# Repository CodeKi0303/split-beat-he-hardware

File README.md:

# Split-Beat HE · Hardware

codeki lab의 좌우 분리형 홀 이펙트 리듬게임 컨트롤러입니다. C86 4층 PCB는 좌우 각각 Hall 입력 7개와 기계식 입력·인코더를 지원합니다.

## 한 세트 주문

1. [PCB 제작 자료](manufacturing/pcb)의 Gerber/드릴 ZIP, BOM, CPL을 업로드합니다. 한 패널에 왼쪽과 오른쪽 각 1장이 들어 있습니다. 업체의 최소 수량과 실장 후 분리 옵션을 확인하세요.
2. 4층 1.6mm급, ENIG, 신호–GND–GND–신호 구성으로 견적을 받습니다. 제작 전 USB HS 차동 90Ω 목표와 공장 적층을 대조하고, **R609 한 자리만 미실장**과 하단 SWD 직각 헤더의 **긴 핀이 기판 안쪽**을 향하는지 확인합니다. KiCad 원본에 R609 패드가 남아 있습니다. CPL의 좌우 수직 노브 인코더와 SWD 헤더를 공장 DFM에서 확인하고, 수평 휠 TTC 엔코더는 별도로 구매해 직접 납땜합니다.
3. 알루미늄 5052 1.5mm [실제 조립 판](manufacturing/plates/as-built)을 상판 좌우·하판 좌우 각 1장 주문합니다. 상판은 은색 무광 아노다이징, 하판은 무처리로 제작했습니다. 상·하판 외곽을 맞춘 [수정 후보](manufacturing/plates/fit-candidate)는 실제 출력·조립 확인이 남아 있습니다.
4. [수평 휠 저장소](https://github.com/CodeKi0303/split-beat-he-wheel)에서 휠과 지지부, MR83ZZ 베어링, TTC Gold 엔코더 규격을 확인합니다. 수직 노브용 [베젤](manufacturing/knob-bezels), 스위치와 키캡, 나사·절연 와셔·스페이서도 준비합니다.

제작 묶음은 원본 업로드 자료의 공개용 복사본입니다. 공장 내부 CAM·견적·주문 화면과 계정 자료는 별도로 관리합니다. [PCB 제작 메모](manufacturing/pcb/README.md)에서 패널 분리와 실장 조건을 확인하세요.

## 조립과 사용

- [나사 체결 단면도](docs/fastener-assembly-sections.svg)의 A/B/C 위치를 기준으로 조립합니다. USB 개구부, 납땜 핀과 하판의 간격, 휠이 자유롭게 도는지 확인합니다.
- 새 보드는 [펌웨어의 SWD 초기 설치](https://github.com/CodeKi0303/split-beat-he-firmware/blob/main/C86-FIRST-FLASH.md)를 진행합니다.
- **PC → 왼쪽 PC용 USB-C**, **왼쪽 split 포트 → 오른쪽 split 포트** 순으로 연결합니다. 오른쪽 USB-C는 좌우 통신·전원용입니다. [Studio](https://studio.codekilab.com/)에서 캘리브레이션, 매핑, 작동점 및 Rapid Trigger를 설정합니다. [Studio 소스와 로컬 실행](https://github.com/CodeKi0303/split-beat-he-studio).

## 휠 가져오기

```sh
git clone --recurse-submodules https://github.com/CodeKi0303/split-beat-he-hardware.git
```

이미 내려받았다면 `git submodule update --init`으로 `modules/horizontal-wheel`을 받습니다. 서브모듈이 이 설계에 맞춰 검토한 휠 커밋을 고정합니다.

직접 만든 설계는 [CERN-OHL-P-2.0](LICENSE)입니다. `pcb/board/pcb-libs/`의 외부 풋프린트 고지는 해당 디렉터리에 보존합니다. 프로젝트 이력은 [codeki lab](https://codekilab.com/#keyboard-project)에서 볼 수 있습니다.

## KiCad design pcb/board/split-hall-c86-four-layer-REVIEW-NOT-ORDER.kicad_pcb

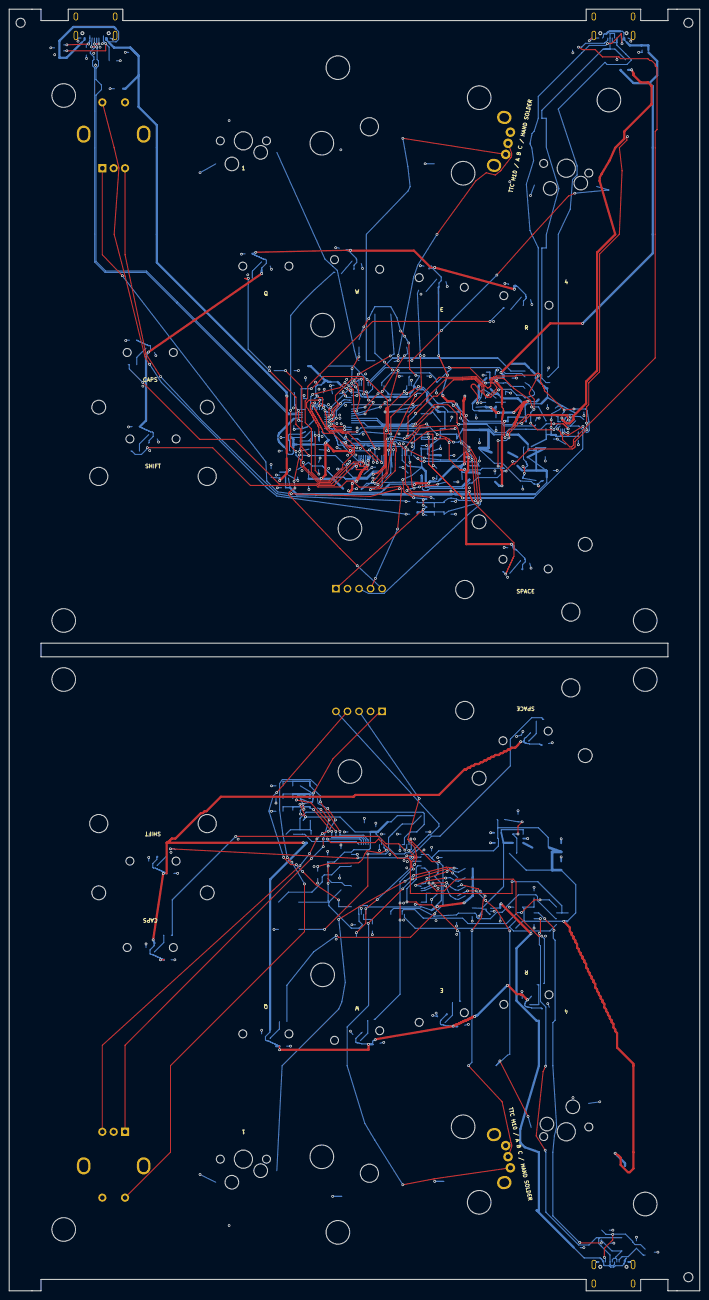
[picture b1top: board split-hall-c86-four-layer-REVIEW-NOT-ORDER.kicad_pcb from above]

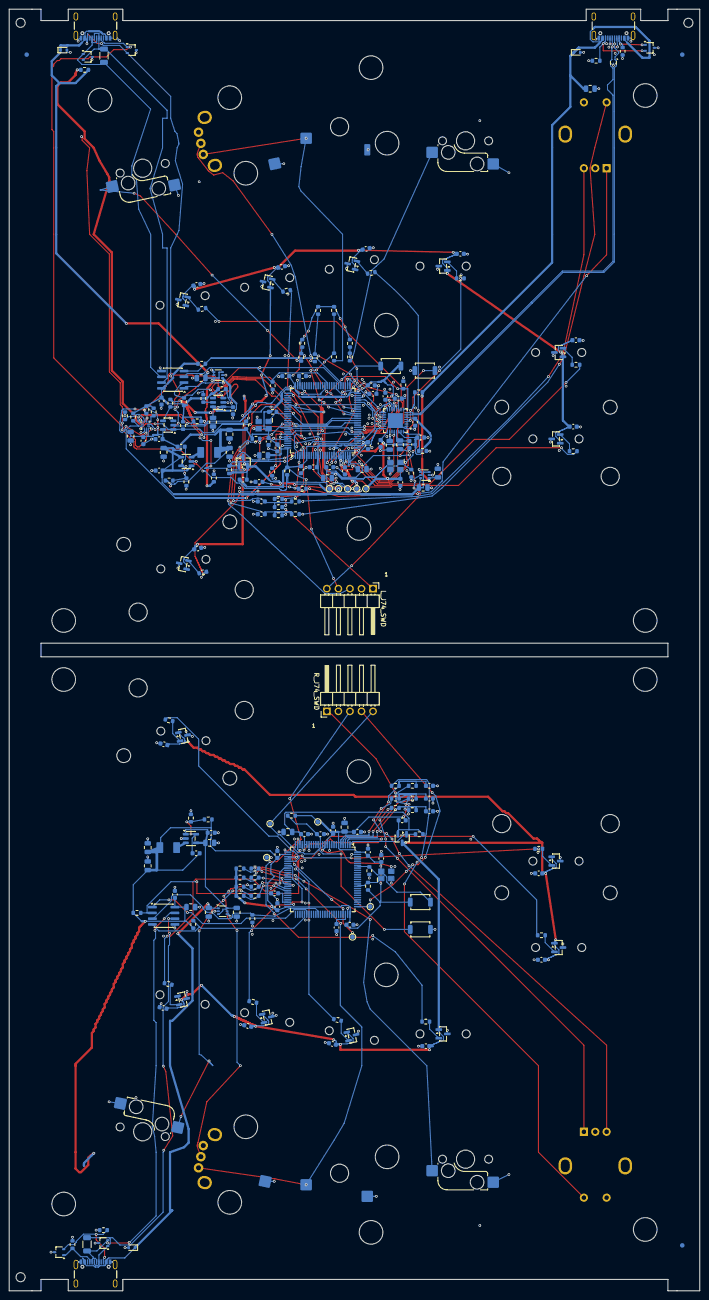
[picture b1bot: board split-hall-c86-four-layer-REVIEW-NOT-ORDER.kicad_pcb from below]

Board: 4 copper layers, 152.0 x 282.1 mm, 307 parts (236 on the bottom side), 143 nets.

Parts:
C211, C212, C221, C230, C231, C232, C233, C234, C236, C239, C311, C312, C321, C330, C331, C332, C333, C334, C336, C339, C410, C411, C412, C413, C414, C416, C418, C501, C551, C607, C608, C701, C1001, C1002, C1003, C1004, C1005, C1006, C1007, C1101, C1102, C1103, C1104, C1105, C1106, C1107: GRM188R72A104KA35D; C_0603_1608Metric
C220, C235, C320, C335, C415, C417: C0805C475K4RACTU; C_0805_2012Metric
C222, C223, C322, C323: GRM21BR71C106KE51L; C_0805_2012Metric
C237, C238, C337, C338: GRM188R71A225KE15D; C_0603_1608Metric
C240, C340, C401, C502, C552, C601, C602, C603, C604, C605, C606, C702: GRM21BR71C105KA01L; C_0805_2012Metric
C1401, C1402, C1403, C1501, C1502, C1503: 1nF; C_0603_1608Metric
D401: TPD2EUSB30ADRTR; Texas_DRT-3
D402, D503, D553: TPD2E2U06DCKR; SOT-323_SC-70
D403, D504, D554: TPD1E10B06DYAR; D_SOD-523
D502, D552: TPD2E007DCKR; SOT-323_SC-70
ENC1401, ENC1501: PEC11R-4215F-S0024; Bourns_PEC11R_4215F_S0024_Centered
FB210, FB310: BLM18PG121SN1D; L_0603_1608Metric
J401, J501, J551: USB4105-GF-A-120; USB_C_Receptacle_GCT_USB4105-xx-A_16P_TopMnt_Horizontal_JLC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
L220, L320: 74437324022; L_Wuerth_74437324022
L_C43_CS1, L_C43_CS2: M3 L5 sleeve / NPTH5.2; MountingHole_3.3mm_C35_M3Stack
L_C77_B1_1, L_C77_B1_2, L_C77_B2_1, L_C77_B2_2: M3 sleeve OD4 L8 / bearing post NPTH5.2; MountingHole_5.2mm_C77_BearingPost
L_C224: 6.8pF; C_0603_1608Metric
L_H1001A, L_H1001B, L_H1002A, L_H1002B, L_H1003A, L_H1003B, L_H1004A, L_H1004B, L_H1005A, L_H1005B, L_H1006A, L_H1006B, L_H1007A, L_H1007B: HE_LOCATOR_COMMON_PATTERN
L_H1006S1, L_H1006S2, L_H1006S3, L_H1006S4, L_H1007S1, L_H1007S2, L_H1007S3, L_H1007S4: STABILIZER_COMMON_2U_PATTERN
L_J74_SWD: PZ254R-11-05P; PinHeader_1x05_P2.54mm_Horizontal_C74_D1p1
L_J1202: TTC H10 DIRECT THT + optional wire lands; TTC_H10_Direct_left
L_MH1, L_MH2, L_MH3, L_MH4: M3 L5 sleeve / NPTH5.2
L_TP201: VTREF; TestPoint_Pad_D1.0mm
L_TP202: GND; TestPoint_Pad_D1.0mm
L_TP203: SWDIO; TestPoint_Pad_D1.0mm
L_TP204: SWCLK; TestPoint_Pad_D1.0mm
L_TP205: NRST; TestPoint_Pad_D1.0mm
L_WIRE_L: WIRE PASSAGE D4.0 / NO FASTENER; Roller_WirePassage_D4mm
PANEL_FID1, PANEL_FID2, PANEL_FID3: BOTTOM PANEL FIDUCIAL 1mm Cu 2mm mask
PANEL_H1, PANEL_H2, PANEL_H3: PANEL TOOLING NPTH 2mm
Q212, Q312: AO3401A; SOT-23
R213, R215, R216, R221, R313, R315, R316, R321, R407, R501, R502, R504, R551, R552, R556, R601, R606, R609: RC0603FR-07100KL; R_0603_1608Metric
R214, R314, R404, R602, R604, R605, R607, R608, R1211, R1212, R1213, R1214, R1311, R1312, R1313, R1314: RC0603FR-0710KL; R_0603_1608Metric
R220, R320: RC0603FR-07453KL; R_0603_1608Metric
R401, R402, R554, R555: RC0603FR-075K1L; R_0603_1608Metric
R403: RC0603FR-07820RL; R_0603_1608Metric
R405: RC0603FR-0712KL; R_0603_1608Metric
R503, R553: 1206W4F1200T5E; R_1206_3216Metric
R603: RC0603JR-070RL; R_0603_1608Metric
R610, R611: RC0603FR-07887KL; R_0603_1608Metric
R701, R702: RC0603FR-074K7L; R_0603_1608Metric
R1001, R1002, R1003, R1004, R1005, R1006, R1007, R1101, R1102, R1103, R1104, R1105, R1106, R1107, R1201, R1202, R1203, R1204, R1301, R1302, R1303, R1304: RC0603FR-071KL; R_0603_1608Metric
R1401, R1402, R1403, R1501, R1502, R1503: 1k; R_0603_1608Metric
R1411, R1412, R1413, R1511, R1512, R1513: 10k; R_0603_1608Metric
R_C43_CS1, R_C43_CS2: M3 L5 sleeve / NPTH5.2; MountingHole_3.3mm_C35_M3Stack
R_C77_B1_1, R_C77_B1_2, R_C77_B2_1, R_C77_B2_2: M3 sleeve OD4 L8 / bearing post NPTH5.2; MountingHole_5.2mm_C77_BearingPost
R_C324: 6.8pF; C_0603_1608Metric
R_H1101A, R_H1101B, R_H1102A, R_H1102B, R_H1103A, R_H1103B, R_H1104A, R_H1104B, R_H1105A, R_H1105B, R_H1106A, R_H1106B, R_H1107A, R_H1107B: HE_LOCATOR_COMMON_PATTERN
R_H1106S1, R_H1106S2, R_H1106S3, R_H1106S4, R_H1107S1, R_H1107S2, R_H1107S3, R_H1107S4: STABILIZER_COMMON_2U_PATTERN
R_J74_SWD: PZ254R-11-05P; PinHeader_1x05_P2.54mm_Horizontal_C74_D1p1
R_J1302: TTC H10 DIRECT THT + optional wire lands; TTC_H10_Direct_right
R_MH1, R_MH2, R_MH3, R_MH4: M3 L5 sleeve / NPTH5.2
R_TP301: VTREF; TestPoint_Pad_D1.0mm
R_TP302: GND; TestPoint_Pad_D1.0mm
R_TP303: SWDIO; TestPoint_Pad_D1.0mm
R_TP304: SWCLK; TestPoint_Pad_D1.0mm
R_TP305: NRST; TestPoint_Pad_D1.0mm
R_WIRE_R: WIRE PASSAGE D4.0 / NO FASTENER; Roller_WirePassage_D4mm
SW210, SW211, SW310, SW311: TS-1088-AR02016; SW_SPST_TS-1088-xR020
SW1201, SW1204, SW1301, SW1304: CPG151101S11; MX_Hotswap_Kailh_CPG151101S11_NPTH
U210, U310: STM32H723VGT6; LQFP-100_14x14mm_P0.5mm
U220, U320: TLV62569DBVR; SOT-23-5
U401: USB3300-EZK; QFN-32-1EP_5x5mm_P0.5mm_EP3.3x3.3mm
U501, U551: THVD1450DR; SOIC-8_3.9x4.9mm_P1.27mm
U601, U603, U606: LM66100DCKR; SOT-363_SC-70-6
U602: TPS2552DBVR; SOT-23-6
U604: FUSB303BTMX; onsemi_QFN12_722AG_1.6x1.6mm_P0.4mm
U605: SN74LVC1G32DBVR; SOT-23-5
U1001, U1002, U1003, U1004, U1005, U1006, U1007, U1101, U1102, U1103, U1104, U1105, U1106, U1107: SS39ET; SOT-23
X210, X310: OXETDLJANF-25MHZ; ECS_3225MV_3.2x2.5mm
X401: ECS-3225MV-240-CN-TR; ECS_3225MV_3.2x2.5mm

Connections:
L_CC_ADDR_STRAP: R611.1, U604.5 (ADDR / 0x47)
L_CC_EN_N: R609.2, U210.45 (PE15), U604.11 (EN_N)
L_CC_ID_N: R604.2, U210.38 (PE8), U604.9 (ID / attach_N), U605.1 (A)
L_CC_INT_N: R605.2, U210.37 (PE7), U604.6 (INT_N)
L_CC_PORT_STRAP: R610.1, U604.3 (PORT / DFP)
L_CC_SCL: R702.2, U210.95 (PB8), U604.8 (SCL)
L_CC_SDA: R701.2, U210.96 (PB9), U604.7 (SDA)
L_CC_VBUS_DET: R603.2, U604.4 (VBUS_DET)
L_GND: C211.2, C212.2, C220.2, C221.2, C222.2, C223.2, C230.2, C231.2, C232.2, C233.2, C234.2, C235.2, C236.2, C237.2, C238.2, C239.2, C240.2, C401.2, C410.2, C411.2, C412.2, C413.2, C414.2, C415.2, C416.2, C417.2, C418.2, C501.2, C502.2, C601.2, C602.2, C603.2, C604.2, C607.2, C608.2, C701.2, C702.2, C1001.2, C1002.2, C1003.2, C1004.2, C1005.2, C1006.2, C1007.2, C1401.2, C1402.2, C1403.2, D401.3 (GND), D402.3 (GND), D403.2 (GND), D502.3 (GND), D503.3 (GND), D504.2 (GND), ENC1401.C (COMMON), ENC1401.MP1 (SHIELD), ENC1401.MP2 (SHIELD), ENC1401.S2 (SW_COMMON), J401.A1 (GND (x4)), J401.A12 (GND (x4)), J401.B1 (GND (x4)), J401.B12 (GND (x4)), J401.SH (SHIELD), J501.A1 (GND (x4)), J501.A12 (GND (x4)), J501.B1 (GND (x4)), J501.B12 (GND (x4)), J501.SH (SHIELD), L_J74_SWD.2, L_J1202.1, L_TP202.1 (GND), R215.2, R221.2, R401.2, R402.2, R404.2, R405.2, R407.2, R501.2, R601.2, R608.2, R611.2, SW210.2, SW1201.2 (GND), SW1204.2 (GND), U210.10 (VSS x5), U210.19 (VSSA), U210.26 (VSS x5), U210.49 (VSS x5), U210.74 (VSS x5), U210.99 (VSS x5), U220.2 (GND), U401.1 (GND + EP33), U401.2 (GND + EP33), U401.33 (GND + EP33), U501.5 (GND), U601.2 (GND), U601.4 (NC), U601.5 (ST unused), U602.2 (GND), U603.2 (GND), U603.4 (NC), U603.5 (ST unused), U604.10 (GND), U605.3 (GND), U1001.3 (GND), U1002.3 (GND), U1003.3 (GND), U1004.3 (GND), U1005.3 (GND), U1006.3 (GND), U1007.3 (GND), X210.2 (GND), X401.2 (GND)
L_LINK_A: D502.1 (A), J501.A6 (D+ (x2)), J501.B6 (D+ (x2)), R503.1, U501.6 (A)
L_LINK_B: D502.2 (B), J501.A7 (D- (x2)), J501.B7 (D- (x2)), R503.2, U501.7 (B)
L_L_3V3: C211.1, C222.1, C223.1, C230.1, C231.1, C232.1, C233.1, C234.1, C235.1, C236.1, C410.1, C411.1, C412.1, C413.1, C418.1, C501.1, C502.1, C607.1, C701.1, C702.1, FB210.1, L220.2, L_C224.1, L_J74_SWD.1, L_TP201.1 (VTREF), R213.1, R214.1, R220.1, R502.1, R504.1, R602.1, R604.1, R605.1, R606.1, R609.1, R610.2, R701.1, R702.1, R1211.1, R1212.1, R1213.1, R1214.1, R1411.1, R1412.1, R1413.1, SW211.1, U210.6 (VBAT), U210.11 (VDD x5), U210.27 (VDD x5), U210.50 (VDD x5), U210.75 (VDD x5), U210.100 (VDD x5), U401.6 (VDD3.3 x4), U401.16 (VDD3.3 x4), U401.25 (VDD3.3 x4), U401.30 (VDD3.3 x4), U401.31 (REG_EN), U501.8 (VCC), U604.12 (VDD), U605.5 (VCC), X210.4 (VDD), X401.4 (VDD)
L_L_5V: C220.1, C221.1, C602.1, C608.1, R607.1, U220.1 (EN), U220.4 (VIN), U601.3 (CE), U601.6 (VOUT), U602.1 (IN)
L_L_A3V3: C239.1, C240.1, FB210.2, Q212.2 (S), R216.1, U210.20 (VREF+), U210.21 (VDDA)
L_L_ADC1: R1001.2, U210.22 (PA0)
L_L_ADC2: R1002.2, U210.23 (PA1)
L_L_ADC3: R1003.2, U210.24 (PA2)
L_L_ADC4: R1004.2, U210.32 (PC4)
L_L_ADC5: R1005.2, U210.33 (PC5)
L_L_ADC6: R1006.2, U210.28 (PA4)
L_L_ADC7: R1007.2, U210.30 (PA6)
L_L_BOOT0: R215.1, SW211.2, U210.94 (BOOT0)
L_L_BUCK_FB: L_C224.2, R220.2, R221.1, U220.5 (FB)
L_L_BUCK_SW: L220.1, U220.3 (SW)
L_L_CC1: D503.1 (CC1), J501.A5 (CC1), U604.1 (CC1)
L_L_CC2: D503.2 (CC2), J501.B5 (CC2), U604.2 (CC2)
L_L_DE: R501.1, U210.61 (PD14), U501.3 (DE)
L_L_HALL1: R1001.1, U1001.2 (OUT)
L_L_HALL2: R1002.1, U1002.2 (OUT)
L_L_HALL3: R1003.1, U1003.2 (OUT)
L_L_HALL3V3: C1001.1, C1002.1, C1003.1, C1004.1, C1005.1, C1006.1, C1007.1, Q212.3 (D), U1001.1 (VCC), U1002.1 (VCC), U1003.1 (VCC), U1004.1 (VCC), U1005.1 (VCC), U1006.1 (VCC), U1007.1 (VCC)
L_L_HALL4: R1004.1, U1004.2 (OUT)
L_L_HALL5: R1005.1, U1005.2 (OUT)
L_L_HALL6: R1006.1, U1006.2 (OUT)
L_L_HALL7: R1007.1, U1007.2 (OUT)
L_L_HALL_EN_N: Q212.1 (G), R216.2, U210.1 (PE2)
L_L_HSE25: U210.12 (PH0), X210.3 (OUT25MHz)
L_L_HSE_EN: R213.2, U210.85 (PD4), X210.1 (OE)
L_L_KEY1_N: R1201.2, R1211.2, U210.40 (PE10)
L_L_KEY4_N: R1204.2, R1214.2, U210.43 (PE13)
L_L_KNOB_A: ENC1401.A, R1401.1
L_L_KNOB_A_GPIO: C1401.1, R1401.2, R1411.2, U210.3 (PE4)
L_L_KNOB_B: ENC1401.B, R1402.1
L_L_KNOB_B_GPIO: C1402.1, R1402.2, R1412.2, U210.4 (PE5)
L_L_KNOB_SW: ENC1401.S1 (SW), R1403.1
L_L_KNOB_SW_GPIO: C1403.1, R1403.2, R1413.2, U210.5 (PE6)
L_L_LINK_RE_N: R504.2, U210.2 (PE3), U501.2 (/RE)
L_L_NRST: C212.1, L_J74_SWD.5, L_TP205.1 (NRST), R214.2, SW210.1, U210.14 (NRST)
L_L_ROLL_A: L_J1202.2, R1202.1
L_L_ROLL_A_GPIO: R1202.2, R1212.2, U210.41 (PE11)
L_L_ROLL_B: L_J1202.3, R1203.1
L_L_ROLL_B_GPIO: R1203.2, R1213.2, U210.42 (PE12)
L_L_RX: U210.56 (PD9), U501.1 (R)
L_L_SW1: R1201.1, SW1201.1 (CONTACT)
L_L_SW4: R1204.1, SW1204.1 (CONTACT)
L_L_SWCLK: L_J74_SWD.4, L_TP204.1 (SWCLK), U210.76 (PA14)
L_L_SWDIO: L_J74_SWD.3, L_TP203.1 (SWDIO), U210.72 (PA13)
L_L_TX: R502.2, U210.55 (PD8), U501.4 (D)
L_L_VCAP1: C237.1, U210.48 (VCAP1)
L_L_VCAP2: C238.1, U210.73 (VCAP2)
L_PC_CC1: D402.1 (CC1), J401.A5 (CC1), R401.1
L_PC_CC2: D402.2 (CC2), J401.B5 (CC2), R402.1
L_PHY_1V8A: C416.1, C417.1, U401.29 (VDDA1.8 analog)
L_PHY_1V8D: C414.1, C415.1, U401.15 (VDD1.8 digital), U401.26 (VDD1.8 digital)
L_PHY_RBIAS: R405.1, U401.32 (RBIAS)
L_PHY_RESET: R404.1, U210.57 (PD10), U401.9 (RESET (HIGH))
L_PHY_VBUS: R403.2, U401.4 (VBUS)
L_PHY_XI: U401.28 (XI), X401.3 (OUT24MHz)
L_PHY_XO_EN: R407.1, U210.81 (PD0), X401.1 (OE)
L_PWR_BLOCK: R606.2, U210.62 (PD15), U605.2 (B)
L_PWR_EN_N: R607.2, U602.3 (/EN), U605.4 (Y = A OR B)
L_PWR_FAULT_N: R602.2, U210.39 (PE9), U602.4 (/FAULT)
L_R_ILIM: R601.1, U602.5 (ILIM)
L_SPLIT_VBUS: C604.1, D504.1 (VBUS), J501.A4 (VBUS (x4)), J501.A9 (VBUS (x4)), J501.B4 (VBUS (x4)), J501.B9 (VBUS (x4)), R603.1, R608.1, U603.3 (CE), U603.6 (VOUT)
L_SW_5V: C603.1, U602.6 (OUT), U603.1 (VIN)
L_ULPI_CLK: U210.29 (PA5), U401.14 (CLKOUT60MHz)
L_ULPI_D0: U210.25 (PA3), U401.24 (DATA0)
L_ULPI_D1: U210.34 (PB0), U401.23 (DATA1)
L_ULPI_D2: U210.35 (PB1), U401.22 (DATA2)
L_ULPI_D3: U210.46 (PB10), U401.21 (DATA3)
L_ULPI_D4: U210.47 (PB11), U401.20 (DATA4)
L_ULPI_D5: U210.51 (PB12), U401.19 (DATA5)
L_ULPI_D6: U210.52 (PB13), U401.18 (DATA6)
L_ULPI_D7: U210.91 (PB5), U401.17 (DATA7)
L_ULPI_DIR: U210.17 (PC2_C), U401.12 (DIR)
L_ULPI_NXT: U210.18 (PC3_C), U401.11 (NXT)
L_ULPI_STP: U210.15 (PC0), U401.13 (STP)
L_USB_HS_DM: D401.2 (D-), J401.A7 (D- (x2)), J401.B7 (D- (x2)), U401.8 (DM)
L_USB_HS_DP: D401.1 (D+), J401.A6 (D+ (x2)), J401.B6 (D+ (x2)), U401.7 (DP)
L_USB_VBUS: C401.1, C601.1, D403.1 (VBUS), J401.A4 (VBUS (x4)), J401.A9 (VBUS (x4)), J401.B4 (VBUS (x4)), J401.B9 (VBUS (x4)), R403.1, U601.1 (VIN)
R_GND: C311.2, C312.2, C320.2, C321.2, C322.2, C323.2, C330.2, C331.2, C332.2, C333.2, C334.2, C335.2, C336.2, C337.2, C338.2, C339.2, C340.2, C551.2, C552.2, C605.2, C606.2, C1101.2, C1102.2, C1103.2, C1104.2, C1105.2, C1106.2, C1107.2, C1501.2, C1502.2, C1503.2, D552.3 (GND), D553.3 (GND), D554.2 (GND), ENC1501.C (COMMON), ENC1501.MP1 (SHIELD), ENC1501.MP2 (SHIELD), ENC1501.S2 (SW_COMMON), J551.A1 (GND (x4)), J551.A12 (GND (x4)), J551.B1 (GND (x4)), J551.B12 (GND (x4)), J551.SH (SHIELD), R315.2, R321.2, R551.2, R554.2, R555.2, R_J74_SWD.2, R_J1302.1 (GND_COMMON), R_TP302.1 (GND), SW310.2, SW1301.2 (GND), SW1304.2 (GND), U310.10 (VSS x5), U310.19 (VSSA), U310.26 (VSS x5), U310.49 (VSS x5), U310.74 (VSS x5), U310.99 (VSS x5), U320.2 (GND), U551.5 (GND), U606.2 (GND), U606.4 (NC), U606.5 (ST unused), U1101.3 (GND), U1102.3 (GND), U1103.3 (GND), U1104.3 (GND), U1105.3 (GND), U1106.3 (GND), U1107.3 (GND), X310.2 (GND)
R_LINK_A: D552.1 (A), J551.A6 (D+ (x2)), J551.B6 (D+ (x2)), R553.1, U551.6 (A)
R_LINK_B: D552.2 (B), J551.A7 (D- (x2)), J551.B7 (D- (x2)), R553.2, U551.7 (B)
R_R_3V3: C311.1, C322.1, C323.1, C330.1, C331.1, C332.1, C333.1, C334.1, C335.1, C336.1, C551.1, C552.1, FB310.1, L320.2, R313.1, R314.1, R320.1, R552.1, R556.1, R1311.1, R1312.1, R1313.1, R1314.1, R1511.1, R1512.1, R1513.1, R_C324.1, R_J74_SWD.1, R_TP301.1 (VTREF), SW311.1, U310.6 (VBAT), U310.11 (VDD x5), U310.27 (VDD x5), U310.50 (VDD x5), U310.75 (VDD x5), U310.100 (VDD x5), U551.8 (VCC), X310.4 (VDD)
R_R_5V: C320.1, C321.1, C606.1, U320.1 (EN), U320.4 (VIN), U606.3 (CE), U606.6 (VOUT)
R_R_A3V3: C339.1, C340.1, FB310.2, Q312.2 (S), R316.1, U310.20 (VREF+), U310.21 (VDDA)
R_R_ADC1: R1101.2, U310.22 (PA0)
R_R_ADC2: R1102.2, U310.23 (PA1)
R_R_ADC3: R1103.2, U310.24 (PA2)
R_R_ADC4: R1104.2, U310.32 (PC4)
R_R_ADC5: R1105.2, U310.33 (PC5)
R_R_ADC6: R1106.2, U310.28 (PA4)
R_R_ADC7: R1107.2, U310.30 (PA6)
R_R_BOOT0: R315.1, SW311.2, U310.94 (BOOT0)
R_R_BUCK_FB: R320.2, R321.1, R_C324.2, U320.5 (FB)
R_R_BUCK_SW: L320.1, U320.3 (SW)
R_R_CC1: D553.1 (CC1), J551.A5 (CC1), R554.1
R_R_CC2: D553.2 (CC2), J551.B5 (CC2), R555.1
R_R_DE: R551.1, U310.61 (PD14), U551.3 (DE)
R_R_HALL1: R1101.1, U1101.2 (OUT)
R_R_HALL2: R1102.1, U1102.2 (OUT)
R_R_HALL3: R1103.1, U1103.2 (OUT)
R_R_HALL3V3: C1101.1, C1102.1, C1103.1, C1104.1, C1105.1, C1106.1, C1107.1, Q312.3 (D), U1101.1 (VCC), U1102.1 (VCC), U1103.1 (VCC), U1104.1 (VCC), U1105.1 (VCC), U1106.1 (VCC), U1107.1 (VCC)
R_R_HALL4: R1104.1, U1104.2 (OUT)
R_R_HALL5: R1105.1, U1105.2 (OUT)
R_R_HALL6: R1106.1, U1106.2 (OUT)
R_R_HALL7: R1107.1, U1107.2 (OUT)
R_R_HALL_EN_N: Q312.1 (G), R316.2, U310.1 (PE2)
R_R_HSE25: U310.12 (PH0), X310.3 (OUT25MHz)
R_R_HSE_EN: R313.2, U310.85 (PD4), X310.1 (OE)
R_R_KEY1_N: R1301.2, R1311.2, U310.40 (PE10)
R_R_KEY4_N: R1304.2, R1314.2, U310.43 (PE13)
R_R_KNOB_A: ENC1501.A, R1501.1
R_R_KNOB_A_GPIO: C1501.1, R1501.2, R1511.2, U310.3 (PE4)
R_R_KNOB_B: ENC1501.B, R1502.1
R_R_KNOB_B_GPIO: C1502.1, R1502.2, R1512.2, U310.4 (PE5)
R_R_KNOB_SW: ENC1501.S1 (SW), R1503.1
R_R_KNOB_SW_GPIO: C1503.1, R1503.2, R1513.2, U310.5 (PE6)
R_R_LINK_RE_N: R556.2, U310.2 (PE3), U551.2 (/RE)
R_R_NRST: C312.1, R314.2, R_J74_SWD.5, R_TP305.1 (NRST), SW310.1, U310.14 (NRST)
R_R_ROLL_A: R1302.1, R_J1302.2 (A_PE11)
R_R_ROLL_A_GPIO: R1302.2, R1312.2, U310.41 (PE11)
R_R_ROLL_B: R1303.1, R_J1302.3
R_R_ROLL_B_GPIO: R1303.2, R1313.2, U310.42 (PE12)
R_R_RX: U310.56 (PD9), U551.1 (R)
R_R_SW1: R1301.1, SW1301.1 (CONTACT)
R_R_SW4: R1304.1, SW1304.1 (CONTACT)
R_R_SWCLK: R_J74_SWD.4, R_TP304.1 (SWCLK), U310.76 (PA14)
R_R_SWDIO: R_J74_SWD.3, R_TP303.1 (SWDIO), U310.72 (PA13)
R_R_TX: R552.2, U310.55 (PD8), U551.4 (D)
R_R_VCAP1: C337.1, U310.48 (VCAP1)
R_R_VCAP2: C338.1, U310.73 (VCAP2)
R_SPLIT_VBUS: C605.1, D554.1 (VBUS), J551.A4 (VBUS (x4)), J551.A9 (VBUS (x4)), J551.B4 (VBUS (x4)), J551.B9 (VBUS (x4)), U606.1 (VIN)

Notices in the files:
parts and their libraries:
C.8: marbastlib CPG151101S11 adapted 2026-09-14: unplated contact bores, no copper reinforcement bridges, 4.0 mm central bore. Socket pads on F in library; Flip to B for top-inserted MX switch. Retain vendor CERN-OHL-P notice.
